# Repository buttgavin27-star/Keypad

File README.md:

# Keypad

Keypad is a 6-key macropad with direct wiring including an OLED screen.

# Case
Made in Autodesk Fusion (or Fusion360)

Here's how it will fit together!

# Schematic
Made with Kicad, using direct wiring

# PCB
Made with Kicad, with direct-pin wiring

# Bill of Materials
- Seed XIAO RP2040 microcontroller
- 6x MX-Style Switches
- 1x0.91 inch OLED display

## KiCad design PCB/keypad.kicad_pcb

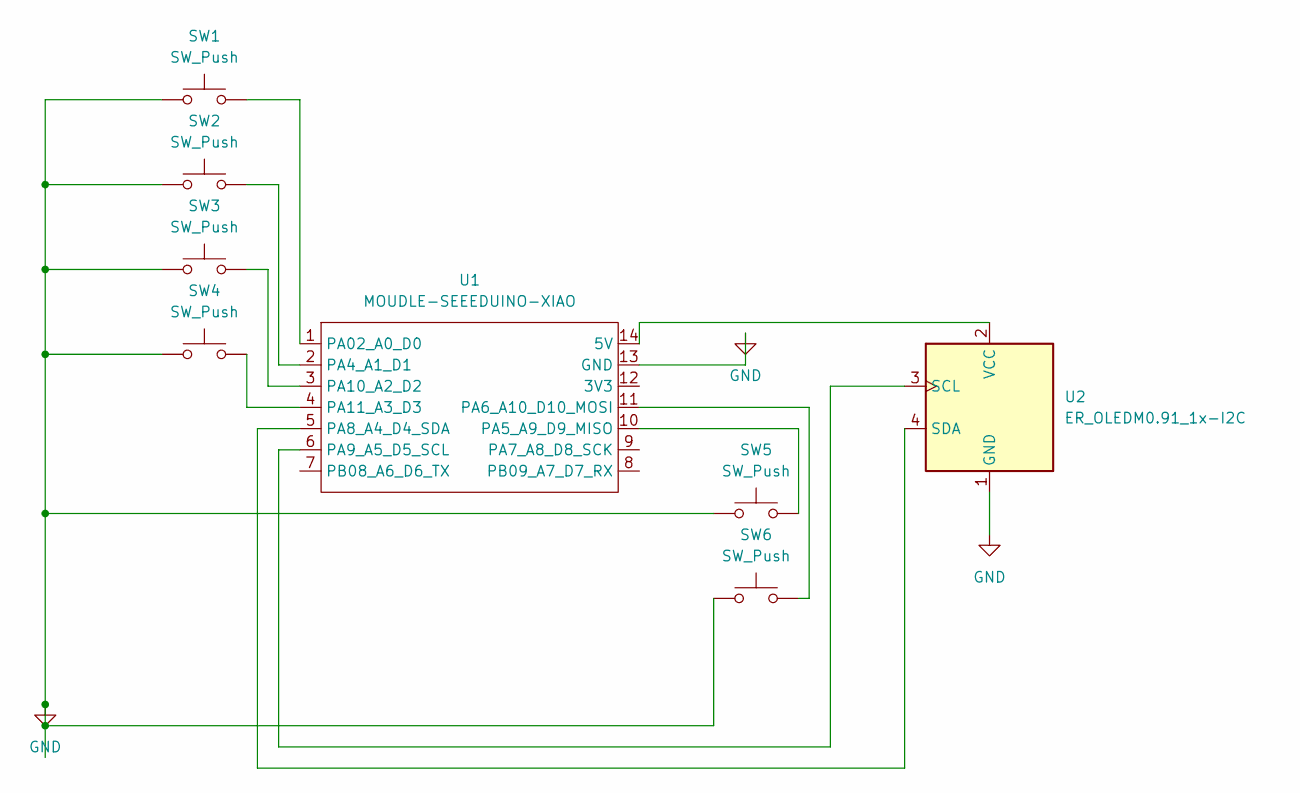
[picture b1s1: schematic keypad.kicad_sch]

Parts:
SW1, SW2, SW3, SW4, SW5, SW6: SW_Push; SW_Cherry_MX_1.00u_PCB
U1: MOUDLE-SEEEDUINO-XIAO; XIAO-Generic-Hybrid-14P-2.54-21X17.8MM
U2: ER_OLEDM0.91_1x-I2C

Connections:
GND: SW1.1, SW2.1, SW3.1, SW4.1, SW5.1, SW6.1, U1.13 (GND), U2.1 (GND)
unnamed: U1.14 (5V), U2.2 (VCC)
unnamed: SW1.2, U1.1 (PA02_A0_D0)
unnamed: SW2.2, U1.2 (PA4_A1_D1)
unnamed: SW5.2, U1.10 (PA5_A9_D9_MISO)
unnamed: SW6.2, U1.11 (PA6_A10_D10_MOSI)
unnamed: U1.5 (PA8_A4_D4_SDA), U2.4 (SDA)
unnamed: U1.6 (PA9_A5_D5_SCL), U2.3 (SCL)
unnamed: SW3.2, U1.3 (PA10_A2_D2)
unnamed: SW4.2, U1.4 (PA11_A3_D3)

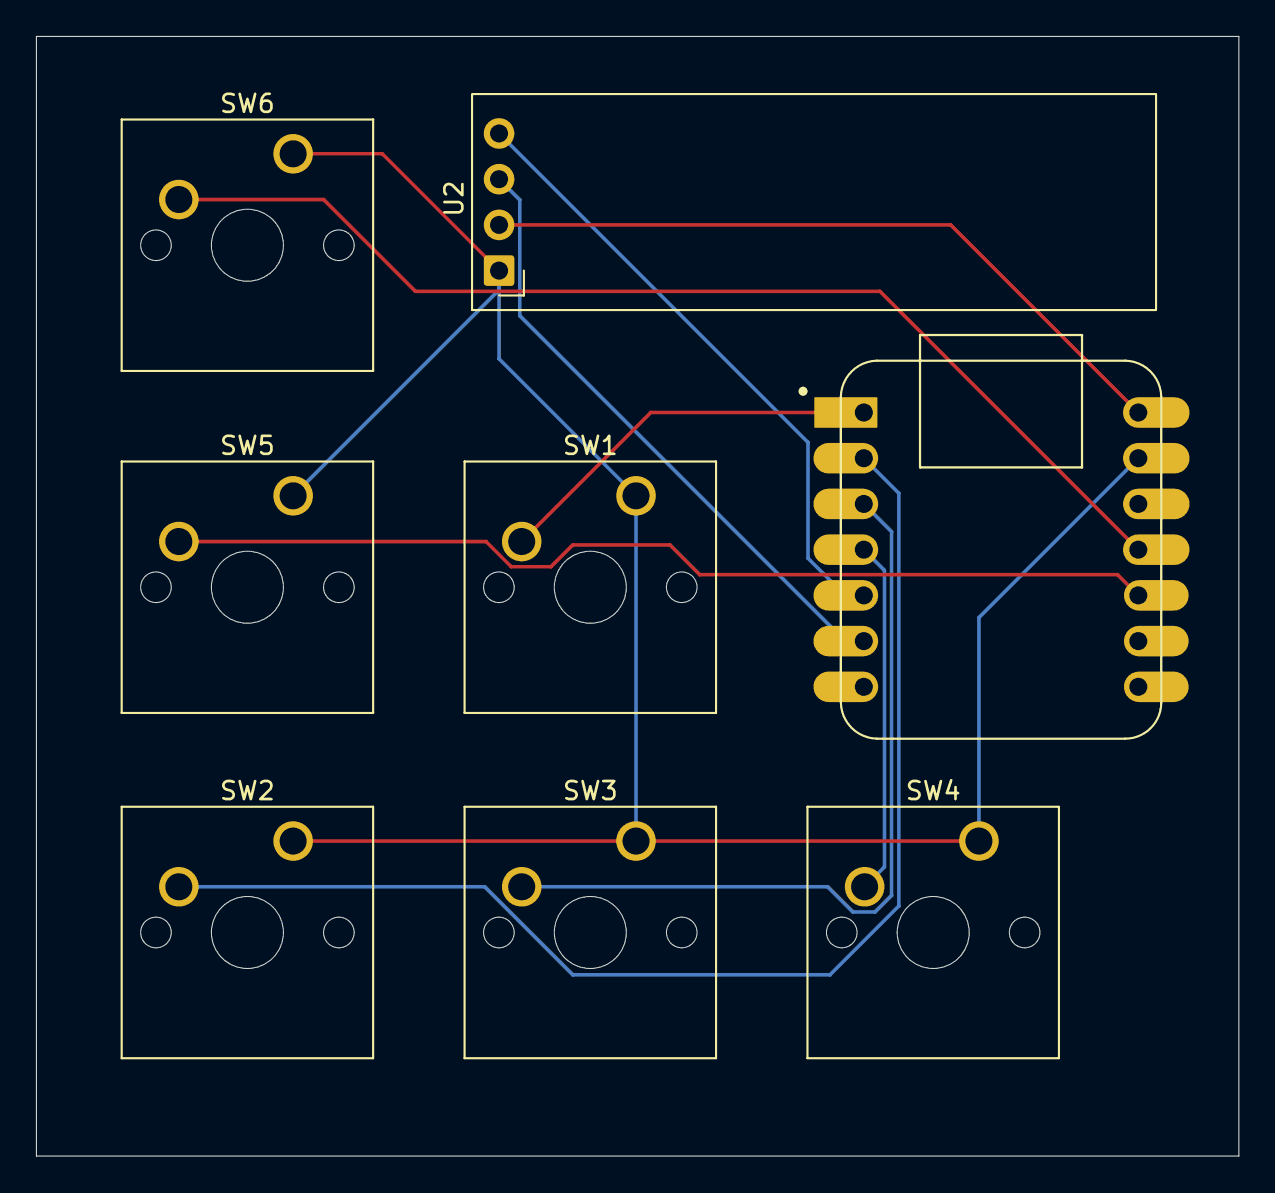
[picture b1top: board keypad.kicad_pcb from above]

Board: 2 copper layers, 66.8 x 62.2 mm, 8 parts (0 on the bottom side), 10 nets.
